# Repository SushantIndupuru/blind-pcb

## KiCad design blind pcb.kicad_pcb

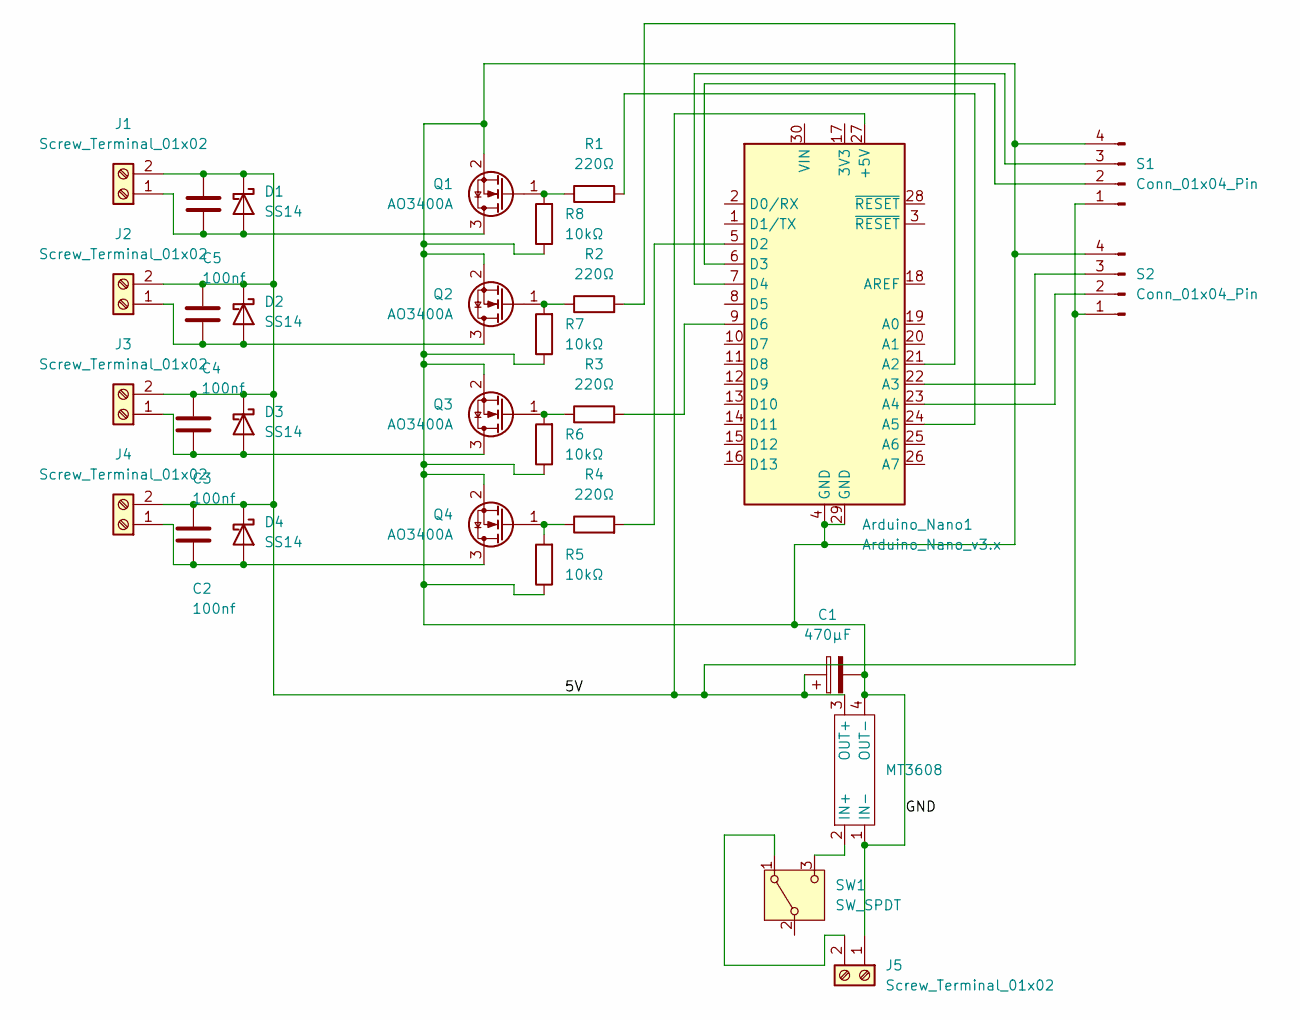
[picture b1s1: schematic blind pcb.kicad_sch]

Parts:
Arduino_Nano1: Arduino_Nano_v3.x; Arduino_Nano
C1: 470µF; CP_Radial_D8.0mm_P2.50mm
C2, C3, C4, C5: 100nf; C_Disc_D4.3mm_W1.9mm_P5.00mm
D1, D2, D3, D4: SS14; D_SMA
J1, J2, J3, J4, J5: Screw_Terminal_01x02; TerminalBlock_MetzConnect_Type059_RT06302HBWC_1x02_P3.50mm_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
MT3608: mt3608
Q1, Q2, Q3, Q4: AO3400A; SOT-23
R1, R2, R3, R4: 220Ω; R_Axial_DIN0207_L6.3mm_D2.5mm_P7.62mm_Horizontal
R5, R6, R7, R8: 10kΩ; R_Axial_DIN0207_L6.3mm_D2.5mm_P7.62mm_Horizontal
S1, S2: Conn_01x04_Pin; PinHeader_1x04_P2.54mm_Vertical
SW1: SW_SPDT; SW_Slide-03_Wuerth-WS-SLTV_10x2.5x6.4_P2.54mm

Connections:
/5V: Arduino_Nano1.27 (+5V), C1.1, C2.1, C3.1, C4.1, C5.1, D1.1 (K), D2.1 (K), D3.1 (K), D4.1 (K), J1.2, J2.2, J3.2, J4.2, MT3608.3 (OUT+), S1.1, S2.1
/GND: Arduino_Nano1.4 (GND), Arduino_Nano1.29 (GND), C1.2, J5.1, MT3608.1 (IN-), MT3608.4 (OUT-), Q1.2 (S), Q2.2 (S), Q3.2 (S), Q4.2 (S), R5.1, R6.1, R7.1, R8.1, S1.4, S2.4
unnamed: Arduino_Nano1.21 (A2), R2.2
unnamed: Arduino_Nano1.22 (A3), S2.3
unnamed: Arduino_Nano1.23 (A4), S2.2
unnamed: Arduino_Nano1.24 (A5), R1.2
unnamed: Arduino_Nano1.5 (D2), R4.2
unnamed: Arduino_Nano1.6 (D3), S1.2
unnamed: Arduino_Nano1.7 (D4), S1.3
unnamed: Arduino_Nano1.9 (D6), R3.2
unnamed: C5.2, D1.2 (A), J1.1, Q1.3 (D)
unnamed: C4.2, D2.2 (A), J2.1, Q2.3 (D)
unnamed: C3.2, D3.2 (A), J3.1, Q3.3 (D)
unnamed: C2.2, D4.2 (A), J4.1, Q4.3 (D)
unnamed: J5.2, SW1.1 (A)
unnamed: MT3608.2 (IN+), SW1.3 (C)
unnamed: Q1.1 (G), R1.1, R8.2
unnamed: Q2.1 (G), R2.1, R7.2
unnamed: Q3.1 (G), R3.1, R6.2
unnamed: Q4.1 (G), R4.1, R5.2

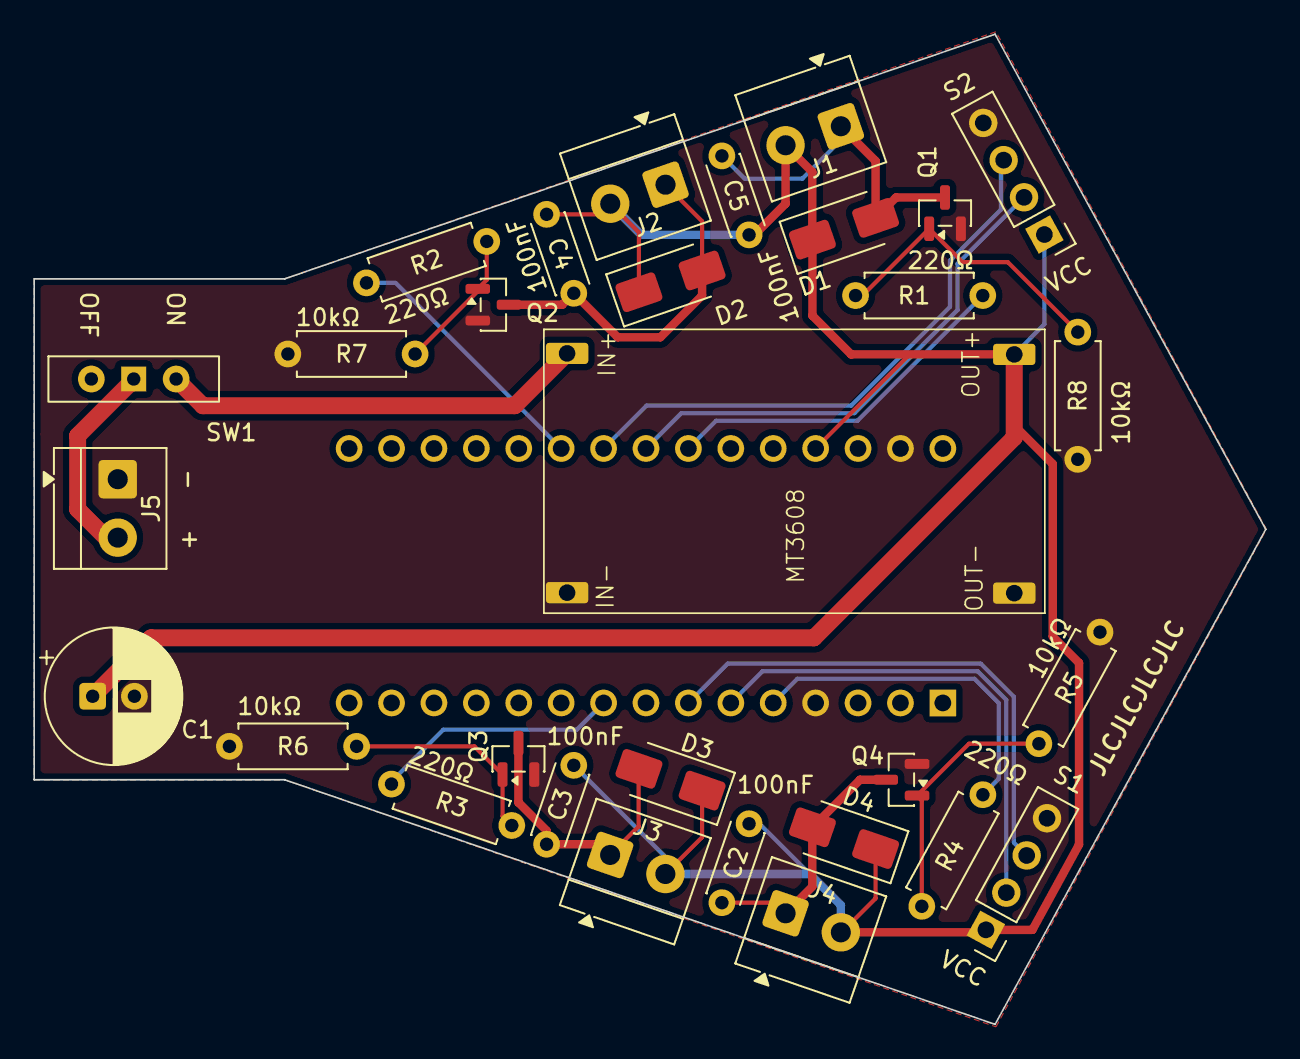
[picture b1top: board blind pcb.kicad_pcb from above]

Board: 2 copper layers, 73.8 x 59.3 mm, 31 parts (1 on the bottom side), 20 nets.

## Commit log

2026-04-18 redesign for wider widths of ultrasonic sensors
2026-04-18 reposition silkscreen
2026-04-18 clean up
2026-04-18 update models
2026-04-19 reroute with ground plane
2026-04-19 refill zone
2026-04-20 reroute
